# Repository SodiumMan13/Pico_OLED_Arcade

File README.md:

# Pico_OLED_Arcade
An OLED module controlled by a Raspberry Pi Pico with fun games for the 4th week of Half-Life.

This project is a gaming system controlled by a Raspberry Pi Pico, shown on an SSD1306 OLED display. It has 5 buttons: up, down, left, right, and select. It contains MicroPython games obtained from YouMakeTech's repository, PicoRetroGamingSystem: https://github.com/YouMakeTech/PicoRetroGamingSystem/blob/main/README.md

The PCB has the Raspberry Pi Pico, the OLED display, a few resistors and capacitors, the 5 tactile switches, a piezo buzzer for sound effects, and an I2C connector for optional sensors.

These are the schematics:

This is the PCB:

This is the 3d render:

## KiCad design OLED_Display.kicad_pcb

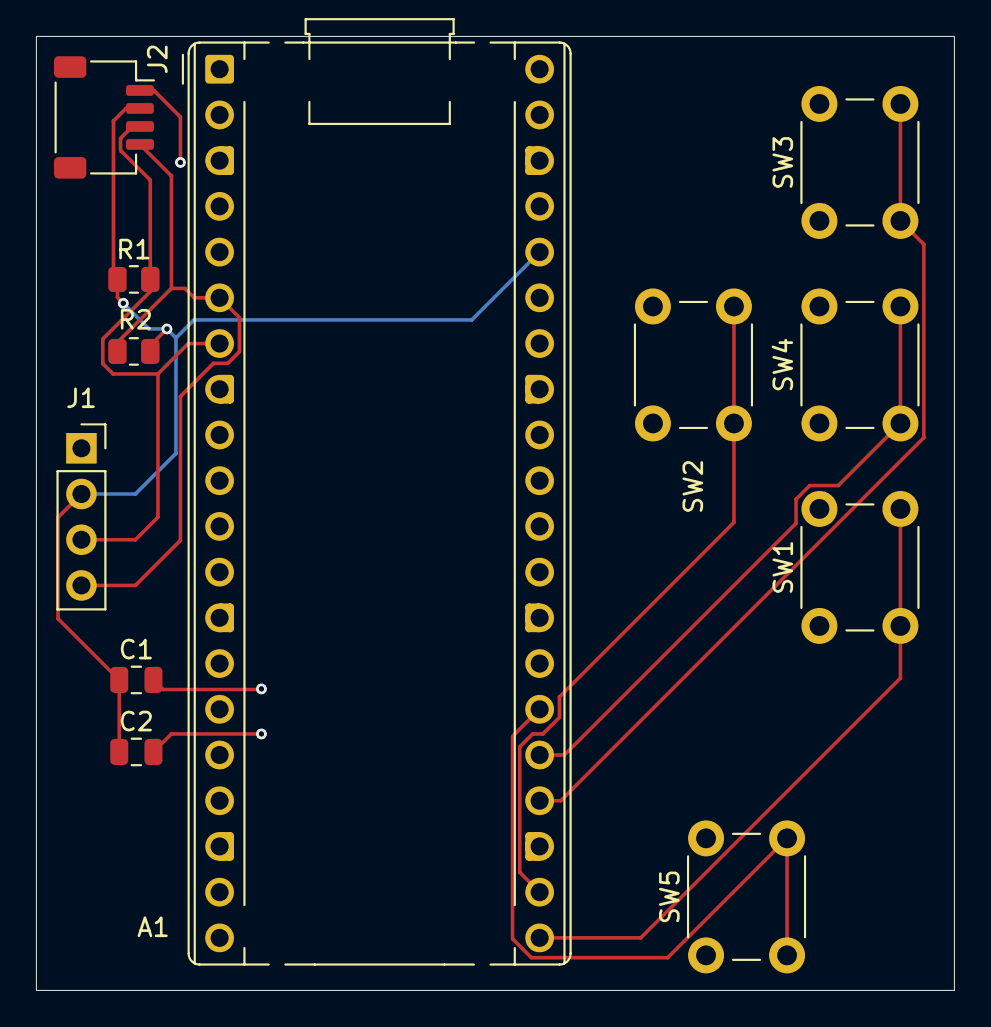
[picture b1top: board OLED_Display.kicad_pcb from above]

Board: 2 copper layers, 51.0 x 53.0 mm, 12 parts (0 on the bottom side), 9 nets.

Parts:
A1: RaspberryPi_Pico; RaspberryPi_Pico_Common_THT
C1: 10uf; C_0805_2012Metric
C2: 100nf; C_0805_2012Metric
J1: Conn_01x04_Pin; PinSocket_1x04_P2.54mm_Vertical
J2: Conn_01x04_Pin; JST_SH_SM04B-SRSS-TB_1x04-1MP_P1.00mm_Horizontal
R1, R2: 47k; R_0805_2012Metric
SW1, SW2, SW3, SW4, SW5: SW_Push; SW_PUSH_6mm_H7.3mm

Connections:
+3.3V: A1.36 (3V3), C1.1, C2.1, J1.2, J2.2, R1.1, R2.1
/BTN_DOWN: A1.25 (GPIO19), SW4.2
/BTN_ENTER: A1.26 (GPIO20), SW5.2
/BTN_LEFT: A1.21 (GPIO16), SW1.2
/BTN_RIGHT: A1.24 (GPIO18), SW3.2
/BTN_UP: A1.22 (GPIO17), SW2.2
/SCL: A1.7 (GPIO5), J1.3, J2.3, R1.2
/SDA: A1.6 (GPIO4), J1.4, J2.4, R2.2
GND: A1.3 (GND), A1.8 (GND), A1.13 (GND), A1.18 (GND), A1.23 (GND), A1.28 (GND), A1.38 (GND), C1.2, C2.2, J1.1, J2.1, SW1.1, SW2.1, SW3.1, SW4.1, SW5.1
